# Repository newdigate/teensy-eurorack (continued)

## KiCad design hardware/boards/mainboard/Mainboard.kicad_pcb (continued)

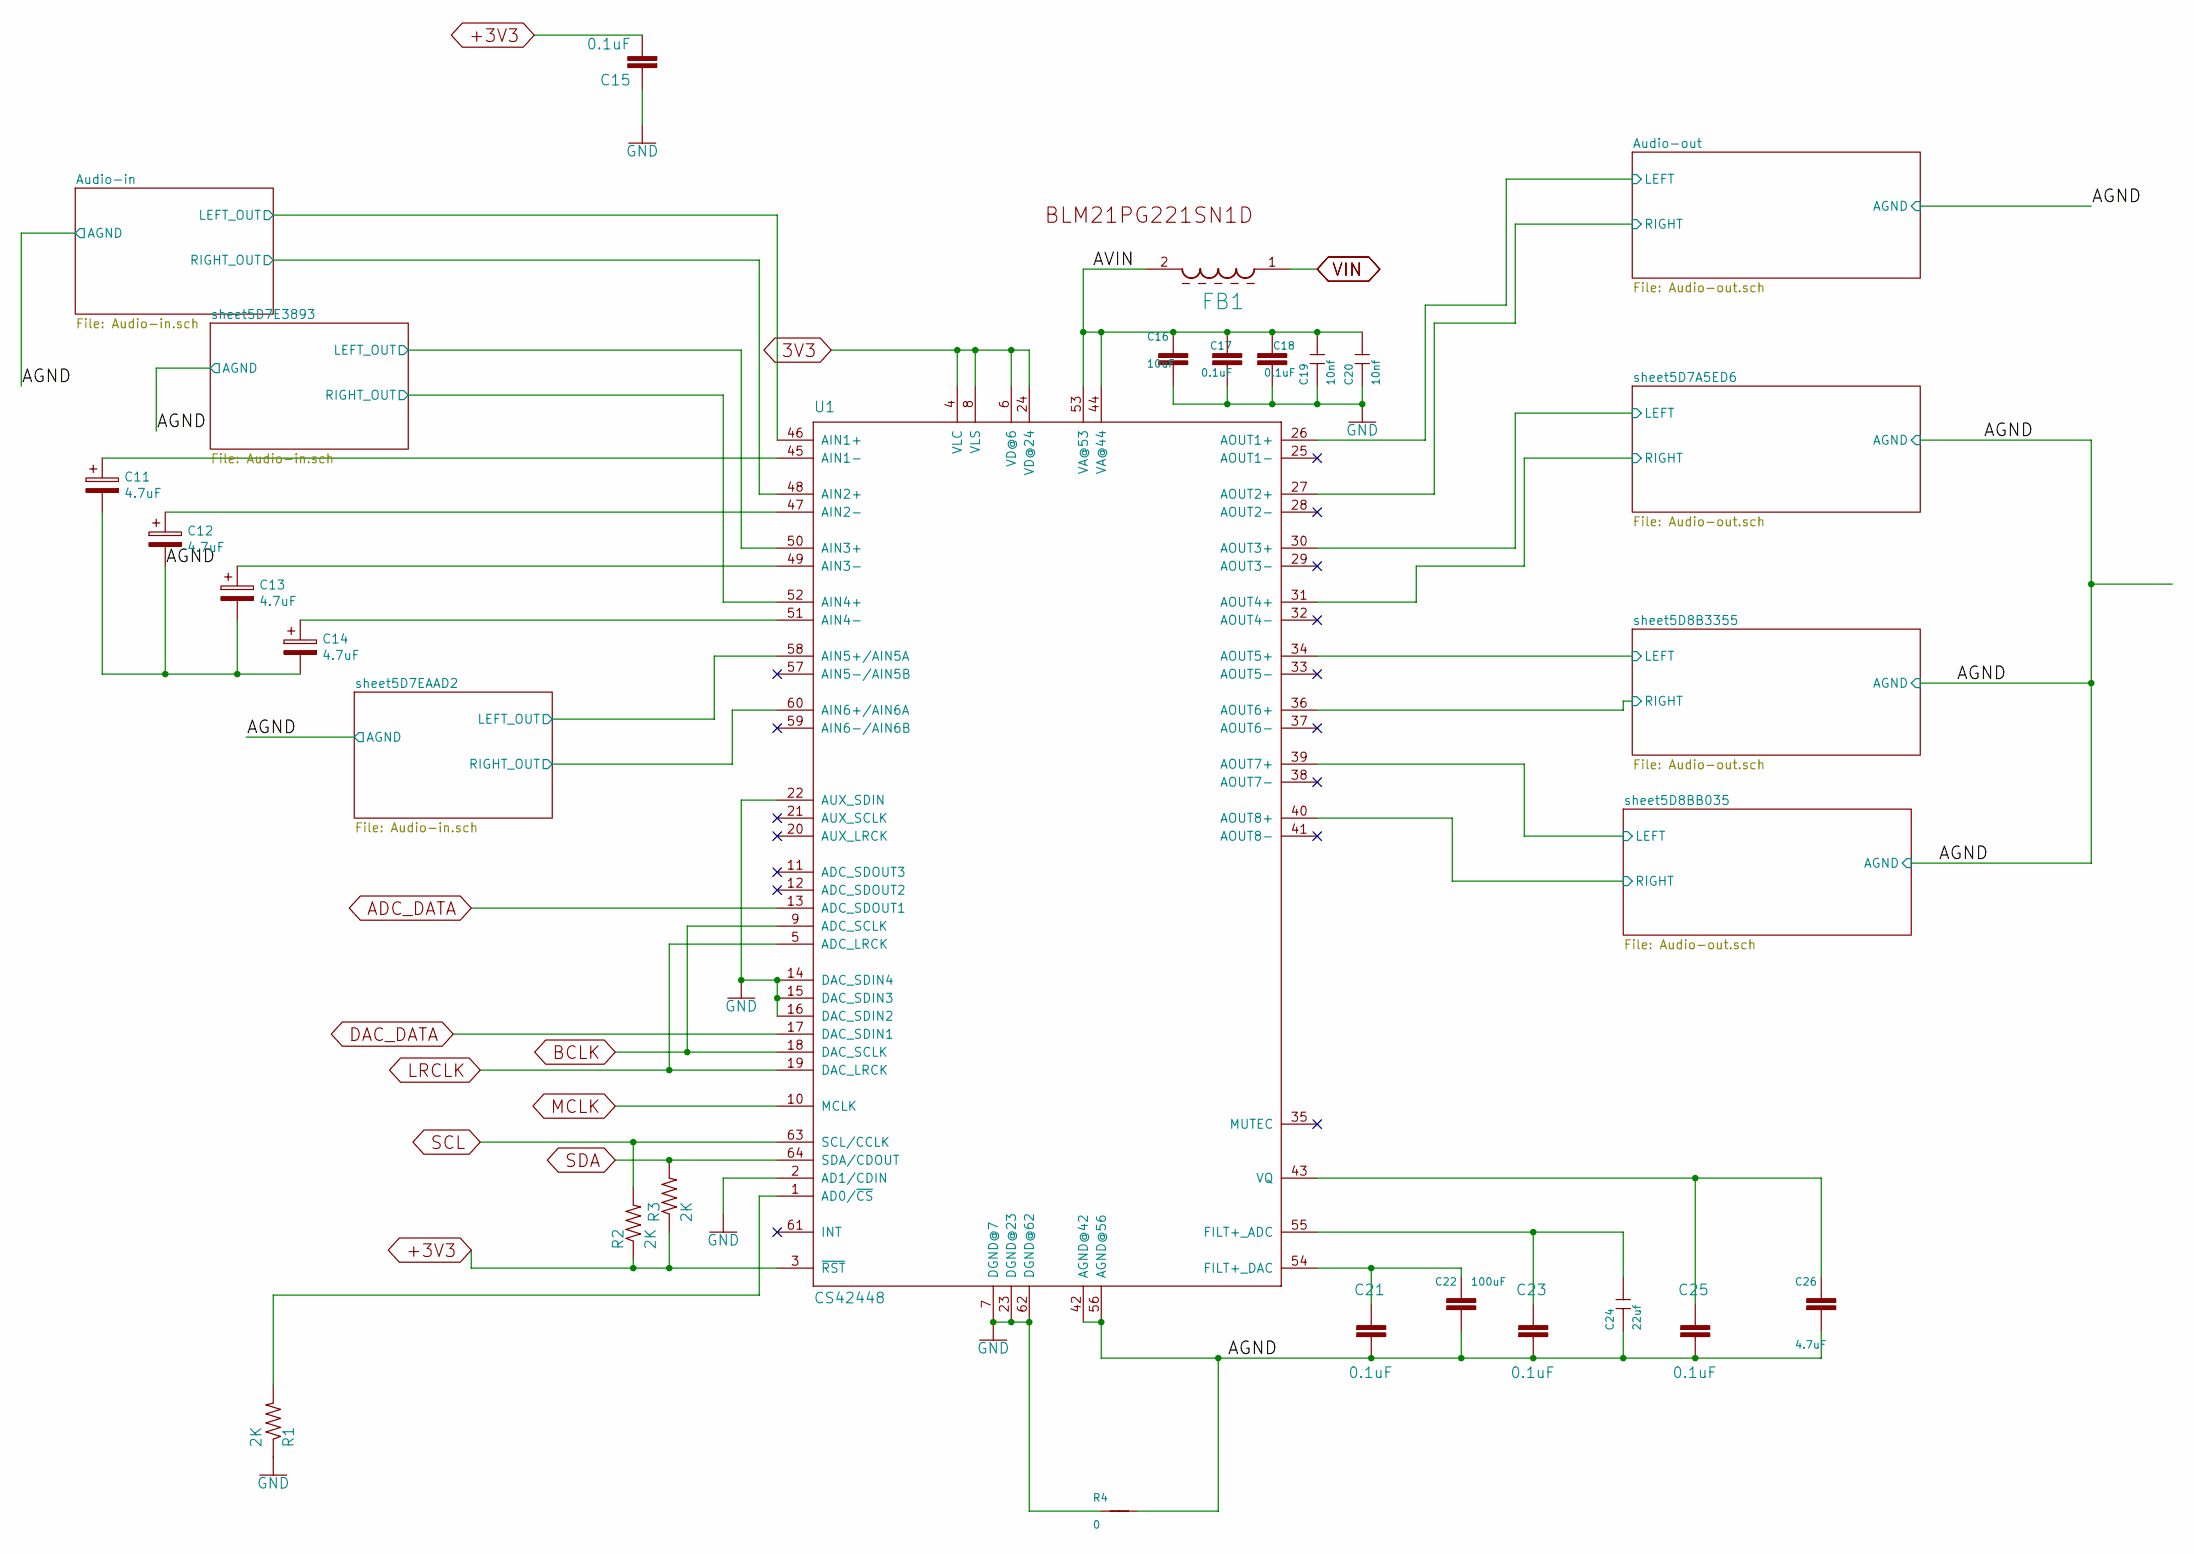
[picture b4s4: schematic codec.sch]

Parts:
C11, C12, C13, C14: 4.7uF; CP_Tantalum_Case-A_EIA-3216-18_Reflow
C15, C17, C18, C21, C23, C25: 0.1uF; C_0805_2012Metric_Pad1.15x1.40mm_HandSolder
C16: 10uF; C_0805_2012Metric_Pad1.15x1.40mm_HandSolder
C19, C20: 10nf; C_0805_2012Metric_Pad1.15x1.40mm_HandSolder
C22: 100uF; C_1206_3216Metric
C24: 22uf; C_0805_2012Metric_Pad1.15x1.40mm_HandSolder
C26: 4.7uF; C_0805_2012Metric_Pad1.15x1.40mm_HandSolder
FB1: MURATA_BLM21PG221SN1DMURATA_BLM21PG221SN1D_0_1; C0805
R1, R2, R3: 2K; R_0805
R4: 0; NetTie-I_Connected_SMD_small
U1: CS42448; LQFP64L

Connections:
3V3: U1.4 (VLC), U1.6 (VD@6), U1.8 (VLS), U1.24 (VD@24); also elsewhere on the board
+3V3: C15.2, R2.1, R3.1, U1.3 (~RST~); also elsewhere on the board
/codec/AVIN: C16.1, C17.1, C18.1, C19.2, C20.2, FB1.2, U1.44 (VA@44), U1.53 (VA@53)
/codec/LEFT: U1.26 (AOUT1+); also elsewhere on the board
/codec/LEFT_1: U1.39 (AOUT7+); also elsewhere on the board
/codec/LEFT_2: U1.34 (AOUT5+); also elsewhere on the board
/codec/LEFT_3: U1.30 (AOUT3+); also elsewhere on the board
/codec/LEFT_OUT_1: U1.58 (AIN5+/AIN5A); also elsewhere on the board
/codec/LEFT_OUT_2: U1.50 (AIN3+); also elsewhere on the board
/codec/RIGHT: U1.27 (AOUT2+); also elsewhere on the board
/codec/RIGHT_1: U1.36 (AOUT6+); also elsewhere on the board
/codec/RIGHT_2: U1.40 (AOUT8+); also elsewhere on the board
/codec/RIGHT_3: U1.31 (AOUT4+); also elsewhere on the board
/codec/RIGHT_OUT: U1.52 (AIN4+); also elsewhere on the board
/codec/RIGHT_OUT_1: U1.48 (AIN2+); also elsewhere on the board
/codec/RIGHT_OUT_2: U1.60 (AIN6+/AIN6A); also elsewhere on the board
ADC_DATA: U1.13 (ADC_SDOUT1); also elsewhere on the board
BCLK: U1.9 (ADC_SCLK), U1.18 (DAC_SCLK); also elsewhere on the board
DAC_DATA: U1.17 (DAC_SDIN1); also elsewhere on the board
GND: C15.1, C16.2, C17.2, C18.2, C19.1, C20.1, R1.1, R4.1, U1.2 (AD1/CDIN), U1.7 (DGND@7), U1.14 (DAC_SDIN4), U1.15 (DAC_SDIN3), U1.16 (DAC_SDIN2), U1.22 (AUX_SDIN), U1.23 (DGND@23), U1.62 (DGND@62); also elsewhere on the board
LRCLK: U1.5 (ADC_LRCK), U1.19 (DAC_LRCK); also elsewhere on the board
MCLK: U1.10 (MCLK); also elsewhere on the board
unnamed: C11.1, U1.45 (AIN1-)
unnamed: C12.1, U1.47 (AIN2-)
unnamed: C13.1, U1.49 (AIN3-)
unnamed: C14.1, U1.51 (AIN4-)
unnamed: C21.1, C22.1, U1.54 (FILT+_DAC)
unnamed: C23.1, C24.2, U1.55 (FILT+_ADC)
unnamed: R1.2, U1.1 (AD0/~CS~)
SCL: R2.2, U1.63 (SCL/CCLK); also elsewhere on the board
SDA: R3.2, U1.64 (SDA/CDOUT); also elsewhere on the board
VIN: FB1.1; also elsewhere on the board

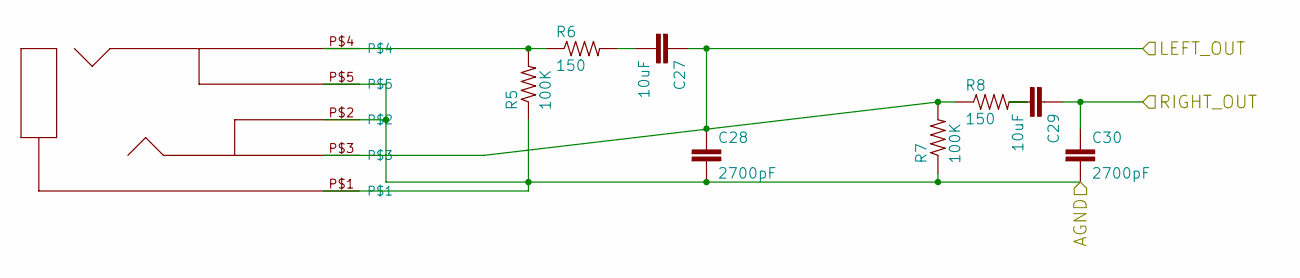
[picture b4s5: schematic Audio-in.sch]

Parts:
C27, C29: 10uF; C_0805_2012Metric_Pad1.15x1.40mm_HandSolder
C28, C30: 2700pF; C_0805_2012Metric_Pad1.15x1.40mm_HandSolder
R5, R7: 100K; R_0805_2012Metric_Pad1.15x1.40mm_HandSolder
R6, R8: 150; R_0805_2012Metric_Pad1.15x1.40mm_HandSolder
U$2: ACJS-MV-5; ACJS-MV5

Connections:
/codec/RIGHT_OUT_1: C29.1, C30.1; also elsewhere on the board
unnamed: C27.2, R6.2
unnamed: C29.2, R8.2
unnamed: R5.2, R6.1, U$2.P$4

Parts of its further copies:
C31, C33, C35, C37: 10uF; C_0805_2012Metric_Pad1.15x1.40mm_HandSolder
C32, C34, C36, C38: 2700pF; C_0805_2012Metric_Pad1.15x1.40mm_HandSolder
R9, R11, R13, R15: 100K; R_0805_2012Metric_Pad1.15x1.40mm_HandSolder
R10, R12, R14, R16: 150; R_0805_2012Metric_Pad1.15x1.40mm_HandSolder
U$3, U$4: ACJS-MV-5; ACJS-MV5

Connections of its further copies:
/codec/LEFT_OUT_1: C35.1, C36.1; also elsewhere on the board
/codec/LEFT_OUT_2: C31.1, C32.1; also elsewhere on the board
/codec/RIGHT_OUT: C33.1, C34.1; also elsewhere on the board
/codec/RIGHT_OUT_2: C37.1, C38.1; also elsewhere on the board
unnamed: C31.2, R10.2
unnamed: C33.2, R12.2
unnamed: C35.2, R14.2
unnamed: C37.2, R16.2
unnamed: R9.2, R10.1, U$3.P$4
unnamed: R11.2, R12.1, U$3.P$3
unnamed: R13.2, R14.1, U$4.P$4
unnamed: R15.2, R16.1, U$4.P$3

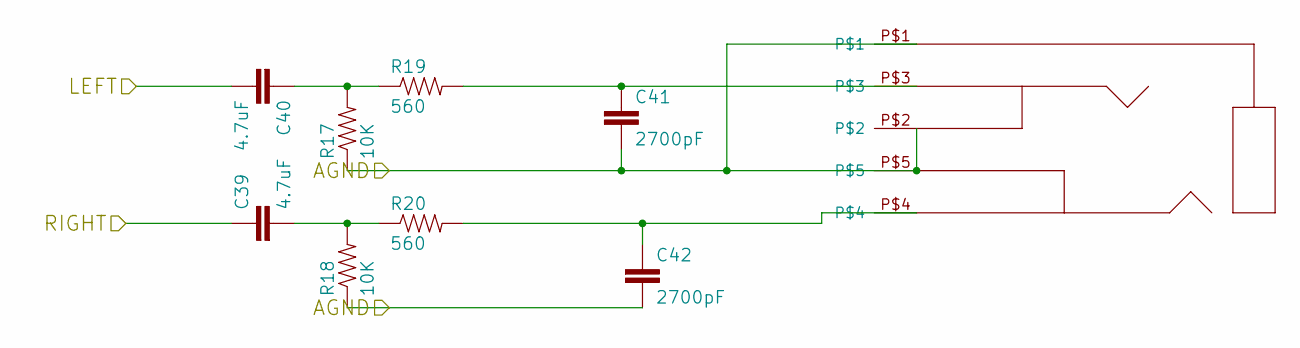
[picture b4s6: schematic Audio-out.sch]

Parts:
C39, C40: 4.7uF; C_0805_2012Metric_Pad1.15x1.40mm_HandSolder
C41, C42: 2700pF; C_0805_2012Metric_Pad1.15x1.40mm_HandSolder
J_OUT1: ACJS-MV-5; ACJS-MV5
R17, R18: 10K; R_0805_2012Metric_Pad1.15x1.40mm_HandSolder
R19, R20: 560; R_0805_2012Metric_Pad1.15x1.40mm_HandSolder

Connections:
/codec/LEFT: C40.2; also elsewhere on the board
/codec/RIGHT: C39.1; also elsewhere on the board
unnamed: C39.2, R18.2, R20.1
unnamed: C40.1, R17.2, R19.1
unnamed: C41.1, J_OUT1.P$3, R19.2
unnamed: C42.1, J_OUT1.P$4, R20.2

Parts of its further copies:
C43, C44, C47, C48, C51, C52: 4.7uF; C_0805_2012Metric_Pad1.15x1.40mm_HandSolder
C45, C46, C49, C50, C53, C54: 2700pF; C_0805_2012Metric_Pad1.15x1.40mm_HandSolder
J_OUT2, J_OUT3, J_OUT4: ACJS-MV-5; ACJS-MV5
R21, R22, R25, R26, R29, R30: 10K; R_0805_2012Metric_Pad1.15x1.40mm_HandSolder
R23, R24, R27, R28, R31, R32: 560; R_0805_2012Metric_Pad1.15x1.40mm_HandSolder

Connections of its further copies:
/codec/LEFT_1: C52.2; also elsewhere on the board
/codec/LEFT_2: C48.2; also elsewhere on the board
/codec/LEFT_3: C44.2; also elsewhere on the board
/codec/RIGHT_1: C47.1; also elsewhere on the board
/codec/RIGHT_2: C51.1; also elsewhere on the board
/codec/RIGHT_3: C43.1; also elsewhere on the board
unnamed: C43.2, R22.2, R24.1
unnamed: C44.1, R21.2, R23.1
unnamed: C45.1, J_OUT2.P$3, R23.2
unnamed: C46.1, J_OUT2.P$4, R24.2
unnamed: C47.2, R26.2, R28.1
unnamed: C48.1, R25.2, R27.1
unnamed: C49.1, J_OUT3.P$3, R27.2
unnamed: C50.1, J_OUT3.P$4, R28.2
unnamed: C51.2, R30.2, R32.1
unnamed: C52.1, R29.2, R31.1
unnamed: C53.1, J_OUT4.P$3, R31.2
unnamed: C54.1, J_OUT4.P$4, R32.2

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
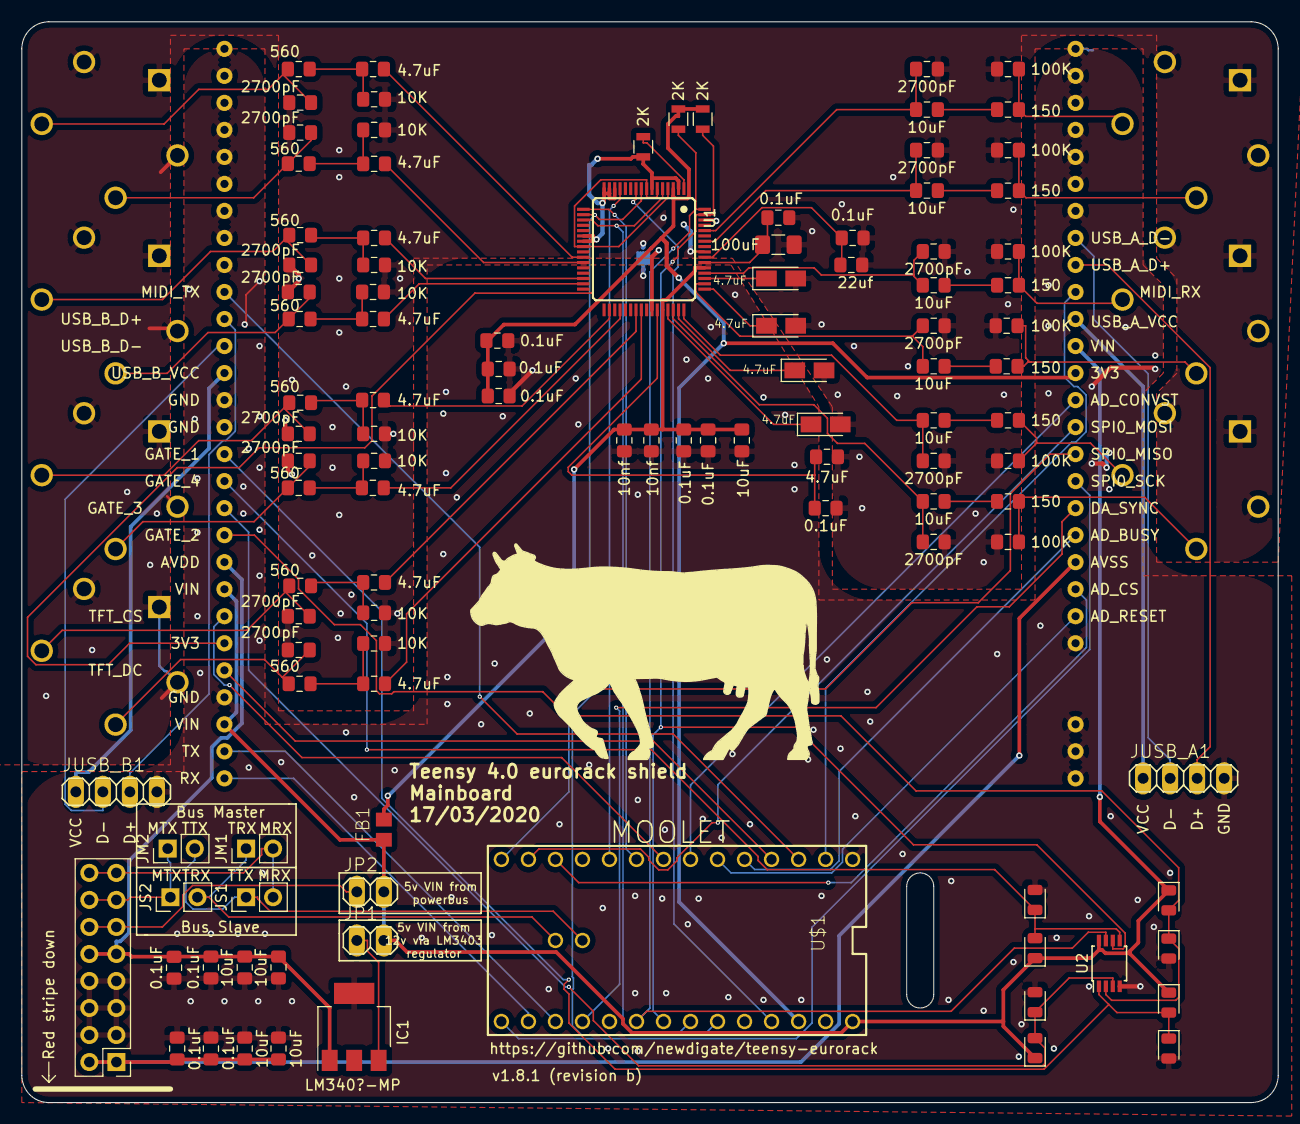
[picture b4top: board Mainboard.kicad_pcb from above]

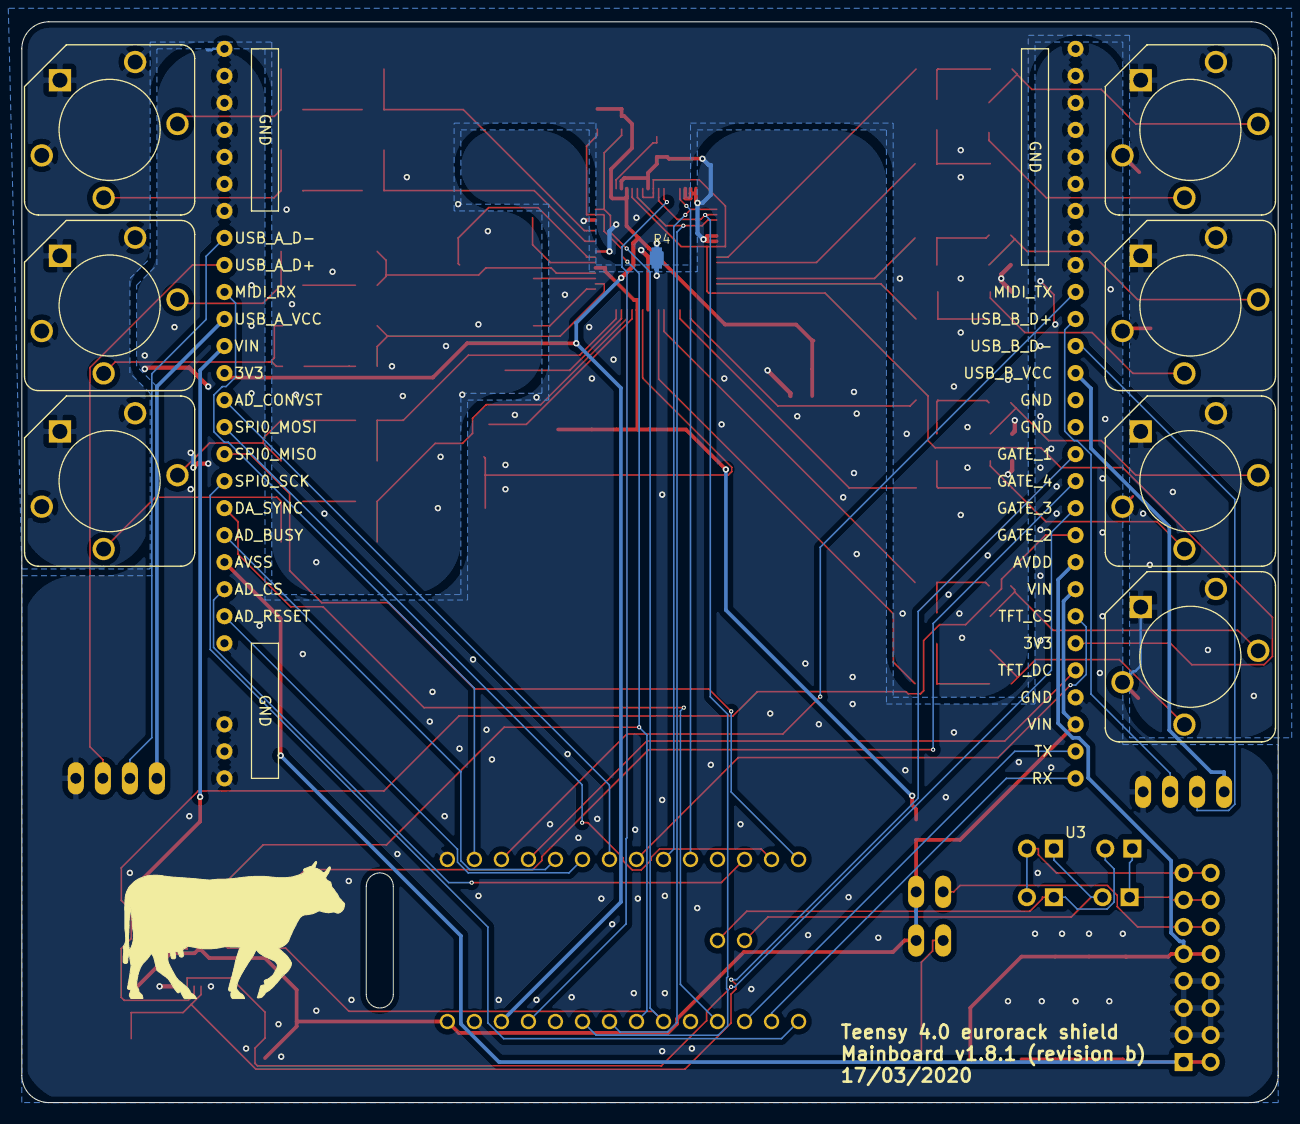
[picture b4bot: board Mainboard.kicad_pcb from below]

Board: 2 copper layers, 118.1 x 101.6 mm, 116 parts (9 on the bottom side), 95 nets.

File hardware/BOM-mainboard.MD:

| Item | Qty | Reference(s)                                                         | Value                    | LibPart                         |                     | price ex-vat | incl vat | total    |
|------|-----|----------------------------------------------------------------------|--------------------------|---------------------------------|---------------------|--------------|----------|----------|
| 1    | 12  | C1, C2, C3, C4, C5, C6, C15, C17, C18, C21, C23, C25                 | 0.1uF                    | 0805                            | C0805C104J5RACTU    | 0.0157       | 0.01884  | 0.22608  |
| 2    | 11  | C7, C8, C9, C10, C16, C27, C29, C31, C33, C35, C37                   | 10uF                     | 0805                            | C0805C104J5RACTU    | £0.020       | £0.024   | £0.264   |
| 3    | 4   | C11, C12, C13, C14                                                   | 4.7uF                    | 0805 Tantalum_Case-A            | TAJP475K016RNJ      | £0.389       | £0.467   | £1.867   |
| 4    | 2   | C19, C20                                                             | 10nf                     | 0805                            | C0805C103J5RACTU    | 0.014        | 0.0168   | 0.0336   |
| 5    | 1   | C22                                                                  | 100uF                    | 1206                            | GRM31CR61A107ME05L  | £0.42        | £0.51    | £0.51    |
| 6    | 1   | C24                                                                  | 22uf                     | 0805                            | CC0805MFX5R5BB226   | 0.334        | 0.4008   | 0.4008   |
| 7    | 9   | C26, C39, C40, C43, C44, C47, C48, C51, C52                          | 4.7uF                    | 0805                            | TAJP475K016RNJ      | 0.389        | 0.4668   | 4.2012   |
| 8    | 14  | C28, C30, C32, C34, C36, C38, C41, C42, C45, C46, C49, C50, C53, C54 | 2700pF                   | 0805                            | C2012C0G1H272J060AA | £0.04        | £0.05    | £0.64    |
| 9    | 8   | D1, D2, D3, D4, D5, D6, D7, D8                                       | TS4148 RYG               | 0805                            | TS4148 RYG          | 0.02         | 0.024    | 0.192    |
| 10   | 1   | FB1                                                                  | BLM21PG221SN1D           | 0805                            | BLM18PG471SN1D      | £0.028       | £0.034   | £0.034   |
| 11   | 1   | IC1                                                                  | SOT-223                  | LM340-MP                        | LM340MP-5.0/NOPB    | 0.854        | 1.0248   | 1.0248   |
| 12   | 7   | J_OUT1, J_OUT2, J_OUT3, J_OUT4, U$2, U$3, U$4                        | ACJS-MV-5                | ACJS-MV-5                       | ACJS-MV-5           | £0.477       | £0.572   | £4.007   |
| 13   | 6   | JM1, JM2, JS1, JS2, JP1, JP2                                         | PINHD-1X2                | PINHD-1X2                       |                     |              | 0        |          |
| 14   | 2   | JUSB_A1, JUSB_B1                                                     | PINHD-1X4                | PINHD-1X4                       |                     |              | 0        |          |
| 15   | 3   | R1, R2, R3                                                           | 2K                       | 0805                            | CRCW08052K00FKEAC   | 0.014        | 0.0168   | 0.0504   |
| 16   | 6   | R5, R7, R9, R11, R13, R15                                            | 100K                     | 0805                            | CRCW0805100KFKEAC   | £0.014       | £0.017   | £0.101   |
| 17   | 6   | R6, R8, R10, R12, R14, R16                                           | 150                      | 0805                            | ERJ-6ENF1500V       | 0.02         | 0.024    | 0.144    |
| 18   | 8   | R17, R18, R21, R22, R25, R26, R29, R30                               | 10K                      | 0805                            | CRCW080510K0FKEAC   | £0.017       | £0.020   | £0.163   |
| 19   | 8   | R19, R20, R23, R24, R27, R28, R31, R32                               | 560                      | 0805                            | RR1220P-561-D       | £0.013       | £0.016   | £0.125   |
| 20   | 1   | SV1                                                                  | EURO_POWER_HEADERREGULAR | PinHeader_2x08_P2.54mm_Vertical |                     |              |          |          |
| 21   | 1   | U1                                                                   | CS42448                  | LQFP64L                         | CS42448-CQZ         | £8.76        | £10.51   | £10.51   |
| 22   | 1   | U2                                                                   | PCA9536                  | TSSOP-8_3x3mm_P0.65mm           | PCA9536DP,118       | £0.72        | £0.86    | £0.86    |
|      |     |                                                                      |                          |                                 |                     |              |          |          |
|      |     |                                                                      |                          |                                 |                     |              |          | 25.35288 |
